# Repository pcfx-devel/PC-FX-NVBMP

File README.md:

# PC-FX-NVBMP

This is a design of a non-volatile backup memory board for the PC-FX. It's based on the
FX-BMP, but doesn't need batteries, and allows for several different sizes.

## Design

I designed the board using the free version of EAGLE, which is limited to 2 layers and
100mm x 100mm board size.  I have included the project files as well as the gerber outputs.

The board design is "Rev_B", as there was a minor fault in the REV_A design.

## Assembly

I have included gerber files, as well as BOM.csv and assembly.csv files, for use with
JLCPCB's SMD assembly service, if you are interested in taking advantage of that.

The second time I tried to order, the MRAM chip was no longer available, and I have noticed
in the past that the empty area would be filled with solder paste and would not be smooth
upon delivery, making it more difficult to solder my own parts on... so I made a special
"empty_MRAM_variant" set of gerbers/BOM.csv/assembly.csv files. The way I used these was to
order boards for assembly (including the level shift, OR gates, voltage regulator, and all the
passive components except the capactiors next to the MRAM chip; I sheared the stencil slightly
above the MRAM chip, and used the stencil to apply solder paste for just the MRAM chip and
2 capacitors, using a hotplate to heat the boards after mounting the missing parts.

The MRAM part in use is MR0A08BCYS35 (TSOP2-44 package), but you could substitute any
other MR0A08... chip which uses the TSOP2-44 package (the 'Y' indicates this).
Additionally, MR2A08... (512KB) or MR4A08... (2MB) chips in the same line will also be
compatible as long as they also use the TSOP2-44 package.

## Case

You can also find the design for a case/enclosure, courtesy of Jeff Chen (Twitter: @jeffqchen).
This is suitable for any 3D printer; I particularly liked the resin prints I ordered online.
The case is designed to accept M2-12 socket-head screws and nuts.

## Circuit Design Concepts

I had originally considered using FRAM (Ferroelectric RAM) as the non-volatile memory type,
but when I went to search for parts, the 28V100 part was out of stock and had increased in
price significantly.  The next choice was MRAM (magnetoresistive RAM), which was available
(in very small quantities), slightly cheaper, and also had larger chips in the line which
shared the same footprint and pinout, so the board could be designed to accommodate the larger
chips without any changes (up to 2MB).

Also important, the pinout of the MRAM chip was very similar to the pinout of the FX-BMP
port, so a 2-layer board coul be made to accommodate it easier than FRAM.

As the PC-FX uses a 5V bus and these chips are based on 3V logic, level-shifters were required.

In order to drive the chip-select (low), a 3-input OR gate is used, requiring the following
lines to ALL be low in order to trigger the chip select:
 1. Cartridge select (keys in on range 0xE8000000 - 0xEFFFFFFF)
 2. A25 (narrows the range to 0xE8000000 - 0xEBFFFFFF)
 3. A24 (narrows the range to 0xE8000000 - 0xE9FFFFFF)

**NOTE:**\
The address lines are numbered according to the chip's address lines, which are not
necessarily the same as the CPU's address lines. The second byte on the memory chip is
actually memory address 0xE8000002, so the memory chip's A0 is effectively the CPU's A1).

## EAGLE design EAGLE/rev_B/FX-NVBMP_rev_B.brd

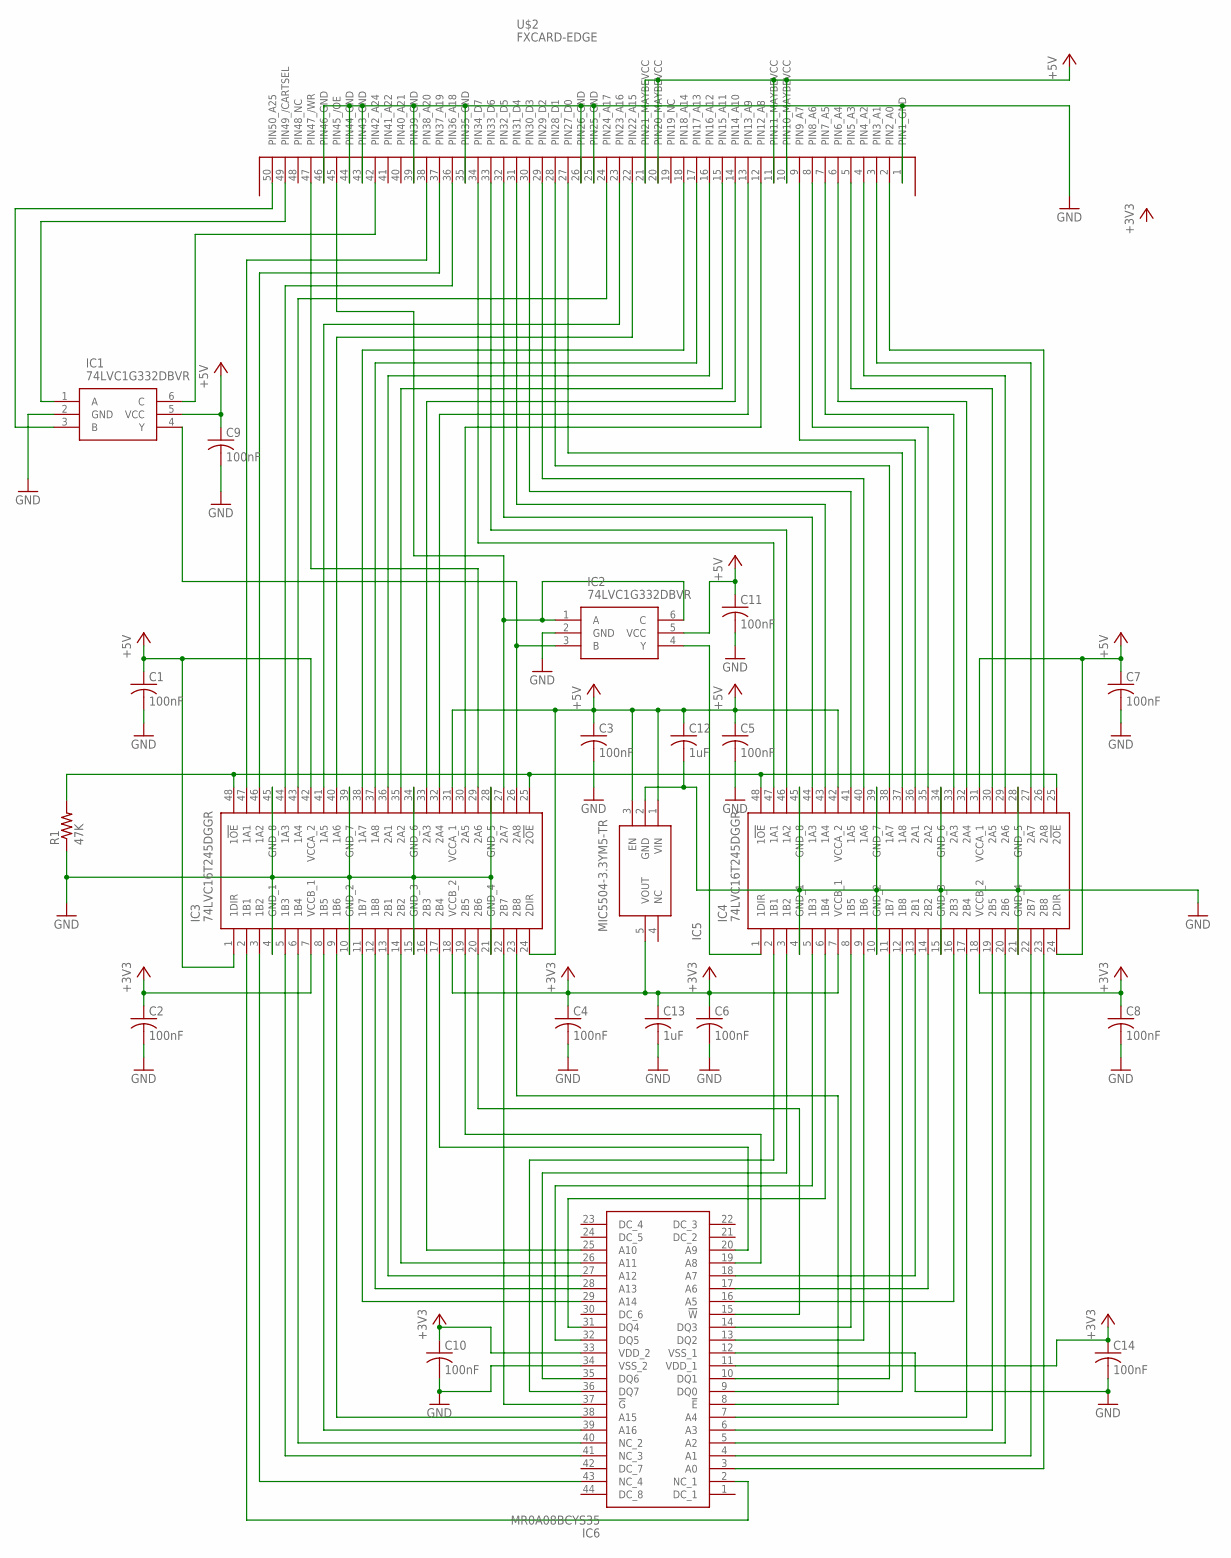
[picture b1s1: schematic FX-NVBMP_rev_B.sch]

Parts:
C1, C2, C3, C4, C5, C6, C7, C8, C9, C10, C11, C14: 100nF; C0402
C12, C13: 1uF; C0402
IC1, IC2: 74LVC1G332DBVR; SOT95P280X145-6N
IC3, IC4: 74LVC16T245DGGR; SOP50P810X120-48N
IC5: MIC5504-3.3YM5-TR; SOT95P280X145-5N
IC6: MR0A08BCYS35; SOP80P1176X120-44N
R1: 47K; R0402
U$2: FXCARD-EDGE

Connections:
+3V3: C2.1, C4.1, C6.1, C8.1, C10.1, C13.1, C14.1, IC3.7 (VCCB_1), IC3.18 (VCCB_2), IC4.7 (VCCB_1), IC4.18 (VCCB_2), IC5.5 (VOUT), IC6.11 (VDD_1), IC6.33 (VDD_2)
+5V: C1.1, C3.1, C5.1, C7.1, C9.1, C11.1, C12.1, IC1.5 (VCC), IC2.5 (VCC), IC3.1 (1DIR), IC3.24 (2DIR), IC3.31 (VCCA_1), IC3.42 (VCCA_2), IC4.24 (2DIR), IC4.31 (VCCA_1), IC4.42 (VCCA_2), IC5.1 (VIN), IC5.3 (EN), U$2.10 (PIN10_MAYBEVCC), U$2.11 (PIN11_MAYBEVCC), U$2.20 (PIN20_MAYBEVCC), U$2.21 (PIN21_MAYBEVCC)
GND: C1.2, C2.2, C3.2, C4.2, C5.2, C6.2, C7.2, C8.2, C9.2, C10.2, C11.2, C12.2, C13.2, C14.2, IC1.2 (GND), IC2.2 (GND), IC3.4 (GND_1), IC3.10 (GND_2), IC3.15 (GND_3), IC3.21 (GND_4), IC3.28 (GND_5), IC3.34 (GND_6), IC3.39 (GND_7), IC3.45 (GND_8), IC4.4 (GND_1), IC4.10 (GND_2), IC4.15 (GND_3), IC4.21 (GND_4), IC4.28 (GND_5), IC4.34 (GND_6), IC4.39 (GND_7), IC4.45 (GND_8), IC5.2 (GND), IC6.12 (VSS_1), IC6.34 (VSS_2), R1.1, U$2.1 (PIN1_GND), U$2.25 (PIN25_GND), U$2.26 (PIN26_GND), U$2.35 (PIN35_GND), U$2.39 (PIN39_GND), U$2.43 (PIN43_GND), U$2.44 (PIN44_GND), U$2.46 (PIN46_GND)
unnamed: IC4.37 (1A8), U$2.27 (PIN27_D0)
unnamed: IC4.38 (1A7), U$2.28 (PIN28_D1)
unnamed: IC4.40 (1A6), U$2.29 (PIN29_D2)
unnamed: IC4.41 (1A5), U$2.30 (PIN30_D3)
unnamed: IC4.43 (1A4), U$2.31 (PIN31_D4)
unnamed: IC4.44 (1A3), U$2.32 (PIN32_D5)
unnamed: IC4.46 (1A2), U$2.33 (PIN33_D6)
unnamed: IC4.47 (1A1), U$2.34 (PIN34_D7)
unnamed: IC4.26 (2A8), U$2.2 (PIN2_A0)
unnamed: IC4.27 (2A7), U$2.3 (PIN3_A1)
unnamed: IC4.29 (2A6), U$2.4 (PIN4_A2)
unnamed: IC4.30 (2A5), U$2.5 (PIN5_A3)
unnamed: IC4.33 (2A3), U$2.7 (PIN7_A5)
unnamed: IC3.43 (1A4), U$2.24 (PIN24_A17)
unnamed: IC4.35 (2A2), U$2.8 (PIN8_A6)
unnamed: IC4.36 (2A1), U$2.9 (PIN9_A7)
unnamed: IC4.32 (2A4), U$2.6 (PIN6_A4)
unnamed: IC3.44 (1A3), U$2.36 (PIN36_A18)
unnamed: IC3.46 (1A2), U$2.37 (PIN37_A19)
unnamed: IC3.47 (1A1), U$2.38 (PIN38_A20)
unnamed: IC1.4 (Y), IC2.3 (B), IC3.26 (2A8)
unnamed: IC3.25 (2!OE), IC3.48 (1!OE), IC4.25 (2!OE), IC4.48 (1!OE), R1.2
unnamed: IC4.23 (2B8), IC6.3 (A0)
unnamed: IC4.22 (2B7), IC6.4 (A1)
unnamed: IC4.20 (2B6), IC6.5 (A2)
unnamed: IC2.4 (Y), IC4.1 (1DIR)
unnamed: IC4.19 (2B5), IC6.6 (A3)
unnamed: IC4.17 (2B4), IC6.7 (A4)
unnamed: IC4.16 (2B3), IC6.16 (A5)
unnamed: IC4.14 (2B2), IC6.17 (A6)
unnamed: IC4.13 (2B1), IC6.18 (A7)
unnamed: IC4.12 (1B8), IC6.9 (DQ0)
unnamed: IC3.30 (2A5), U$2.12 (PIN12_A8)
unnamed: IC3.32 (2A4), U$2.13 (PIN13_A9)
unnamed: IC3.33 (2A3), U$2.14 (PIN14_A10)
unnamed: IC3.35 (2A2), U$2.15 (PIN15_A11)
unnamed: IC3.36 (2A1), U$2.16 (PIN16_A12)
unnamed: IC3.37 (1A8), U$2.17 (PIN17_A13)
unnamed: IC3.38 (1A7), U$2.18 (PIN18_A14)
unnamed: IC3.40 (1A6), U$2.22 (PIN22_A15)
unnamed: IC3.41 (1A5), U$2.23 (PIN23_A16)
unnamed: IC3.29 (2A6), U$2.47 (PIN47_/WR)
unnamed: IC2.1 (A), IC2.6 (C), IC3.27 (2A7), U$2.45 (PIN45_/OE)
unnamed: IC1.3 (B), U$2.50 (PIN50_A25)
unnamed: IC1.1 (A), U$2.49 (PIN49_/CARTSEL)
unnamed: IC1.6 (C), U$2.42 (PIN42_A24)
unnamed: IC4.11 (1B7), IC6.10 (DQ1)
unnamed: IC4.9 (1B6), IC6.13 (DQ2)
unnamed: IC4.8 (1B5), IC6.14 (DQ3)
unnamed: IC4.6 (1B4), IC6.31 (DQ4)
unnamed: IC4.5 (1B3), IC6.32 (DQ5)
unnamed: IC4.3 (1B2), IC6.35 (DQ6)
unnamed: IC4.2 (1B1), IC6.36 (DQ7)
unnamed: IC3.19 (2B5), IC6.19 (A8)
unnamed: IC3.17 (2B4), IC6.20 (A9)
unnamed: IC3.16 (2B3), IC6.25 (A10)
unnamed: IC3.14 (2B2), IC6.26 (A11)
unnamed: IC3.13 (2B1), IC6.27 (A12)
unnamed: IC3.12 (1B8), IC6.28 (A13)
unnamed: IC3.11 (1B7), IC6.29 (A14)
unnamed: IC3.9 (1B6), IC6.38 (A15)
unnamed: IC3.8 (1B5), IC6.39 (A16)
unnamed: IC3.6 (1B4), IC6.40 (NC_2)
unnamed: IC3.5 (1B3), IC6.41 (NC_3)
unnamed: IC3.3 (1B2), IC6.43 (NC_4)
unnamed: IC3.2 (1B1), IC6.2 (NC_1)
unnamed: IC3.20 (2B6), IC6.15 (!W)
unnamed: IC3.23 (2B8), IC6.8 (!E)
unnamed: IC3.22 (2B7), IC6.37 (!G)

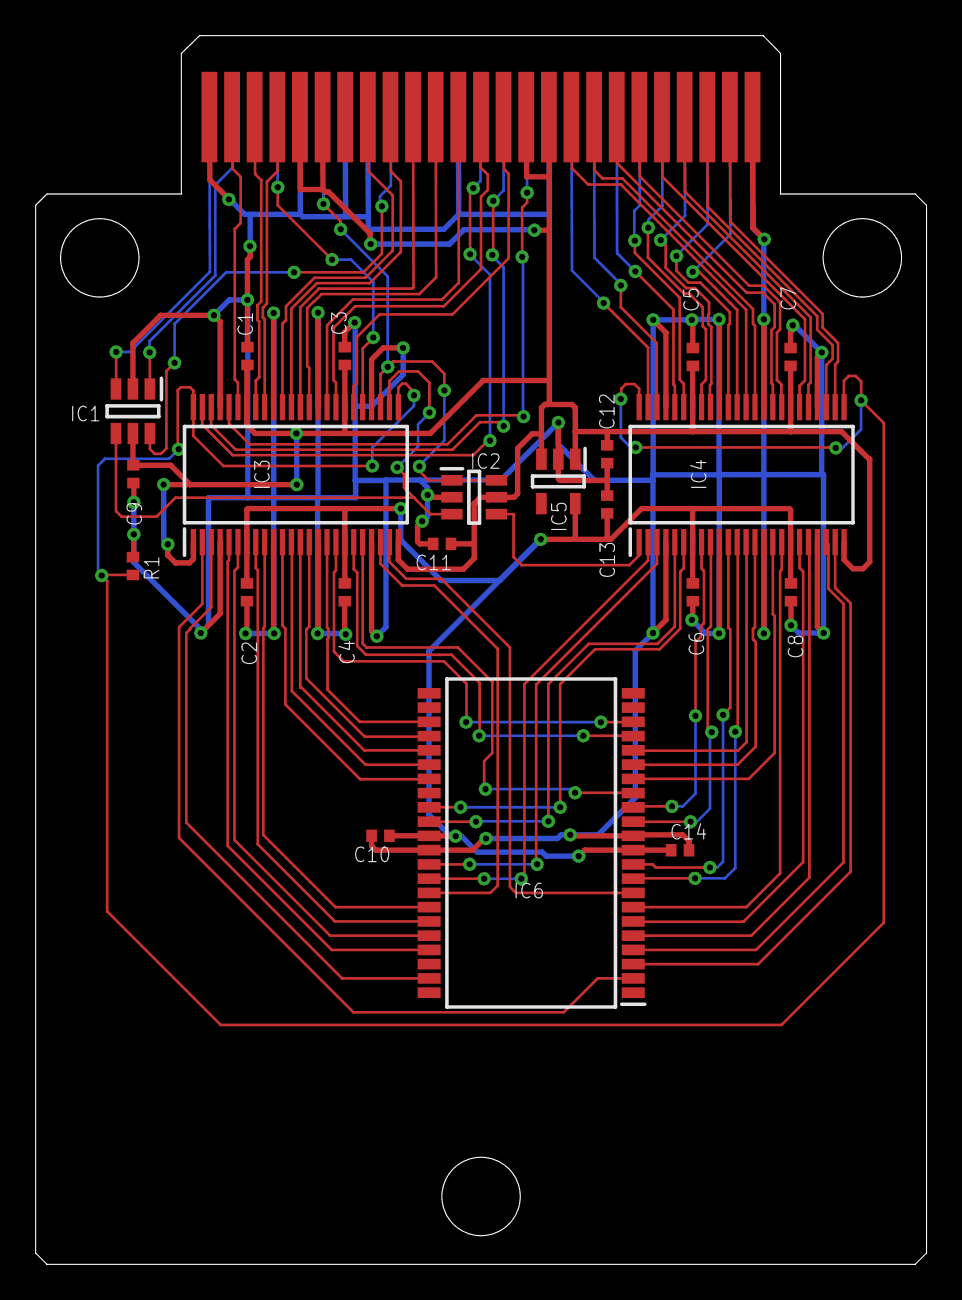
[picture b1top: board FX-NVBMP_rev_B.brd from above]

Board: 2 copper layers, 50.0 x 69.0 mm, 22 parts (0 on the bottom side), 72 nets.

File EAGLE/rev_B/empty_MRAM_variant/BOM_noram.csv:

Qty,Designator,Footprint,Comment,LCSC Part # (optional),Description (optional)
10,"C1, C2, C3, C4, C5, C6, C7, C8, C9, C11",C0402,100nF 16V,C1525,Samsung CL05B104KO5NNNC 100nF 16V 0402
2,"C10, C14",Do Not Populate,Do Not Populate,Do Not Populate,capacitor
2,"C12, C13",C0402,1uF 25V,C52923,Samsung CL05A105KA5NQNC 1uF 25V 0402
1,R1,R0402,47K,C25741,62.5mW Thick Film Resistors 50V ±100ppm/_ ±1% -55_~+155_ 100k½ 0402 Chip Resistor - Surface Mount ROHS
2,"IC3, IC4",TSSOP-48,74LVC16T245DGGR,C148170,"Texas Instruments 74LVC16T245DGGR, Dual, Bus Transceiver, 16-Bit Non-Inverting LVTTL, 1.65  5.5 V, 48-Pin TSSOP"
2,"IC1, IC2",SOT-23-6,74LVC1G332DBVR,C43368,"Texas Instruments 74LVC1G332DBVR, 3-Input OR Logic Gate, 1.65  5.5 V, 6-Pin SOT-23"
1,U$2,Do Not Populate,Do Not Populate,Do Not Populate,Do Not Populate
1,IC5,SOT-23-5,MIC5504-3.3YM5-TR,C88419,300mA 60dB@(1kHz) 380mV@(300mA) Fixed 3.3V~3.3V Positive 1 5.5V SOT-23-5 Linear Voltage Regulators (LDO) ROHS
1,IC6,Do Not Populate,Do Not Populate,Do Not Populate,MRAM

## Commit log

2022-12-17 Fix silkscreen on Rev. B
2022-12-29 Initial release
2022-12-29 Add images

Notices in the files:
EAGLE/rev_B/FX-NVBMP_rev_B.brd:
(c) 2022
